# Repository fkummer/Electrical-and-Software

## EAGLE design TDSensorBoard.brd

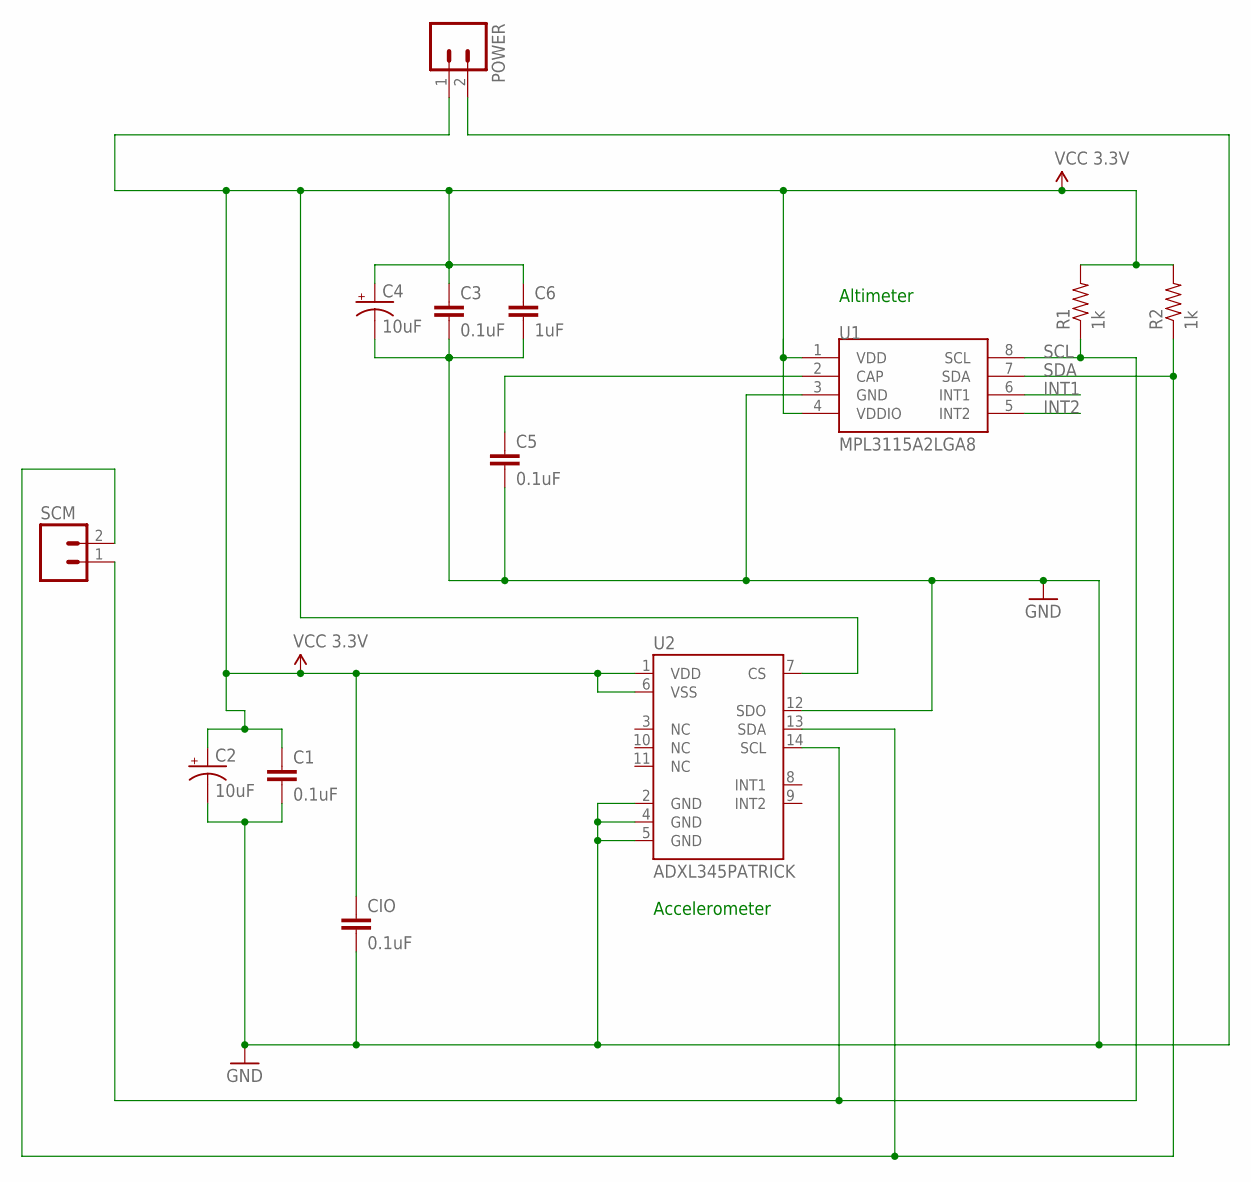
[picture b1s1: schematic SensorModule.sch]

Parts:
C1, C3, C5: 0.1uF; CAP-PTH-SMALL
C2, C4: 10uF; CPOL-RADIAL-10UF-25V
C6: 1uF; CAP-PTH-SMALL
CIO: 0.1uF; CAP-PTH-SMALL
POWER: M02PTH; 1X02
R1, R2: 1k; AXIAL-0.4
SCM: M02PTH; 1X02
U1: MPL3115A2LGA8; LGA8
U2: ADXL345PATRICK; LGA14_1:1_PATRICK

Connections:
GND: C1.2, C2.2 (-), C3.2, C4.2 (-), C5.2, C6.2, CIO.2, POWER.2, U1.3 (GND), U2.2 (GND), U2.4 (GND), U2.5 (GND), U2.12 (SDO)
INT1: U1.6 (INT1)
INT2: U1.5 (INT2)
unnamed: C5.1, U1.2 (CAP)
SCL: R1.P$1 (1), SCM.1, U1.8 (SCL), U2.14 (SCL)
SDA: R2.P$1 (1), SCM.2, U1.7 (SDA), U2.13 (SDA)
VCC_3.3V: C1.1, C2.1 (+), C3.1, C4.1 (+), C6.1, CIO.1, POWER.1, R1.P$2 (2), R2.P$2 (2), U1.1 (VDD), U1.4 (VDDIO), U2.1 (VDD), U2.6 (VSS), U2.7 (CS)

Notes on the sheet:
Altimeter
Accelerometer

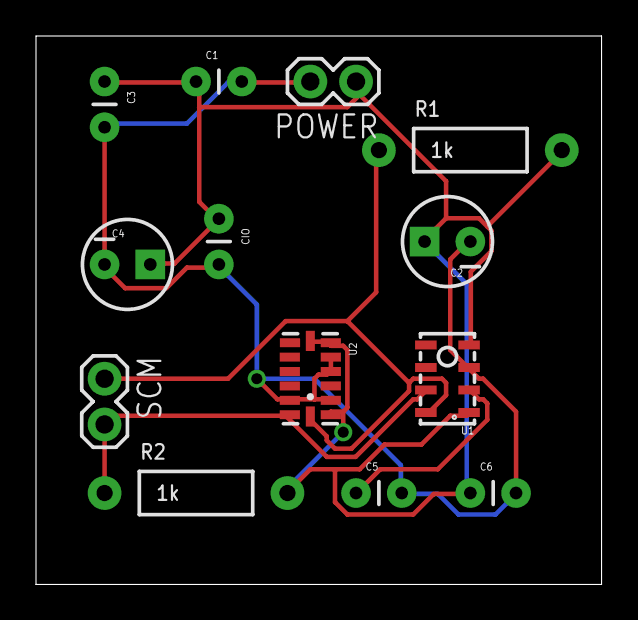
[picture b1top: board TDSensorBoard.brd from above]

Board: 2 copper layers, 31.4 x 30.5 mm, 13 parts (0 on the bottom side), 5 nets.

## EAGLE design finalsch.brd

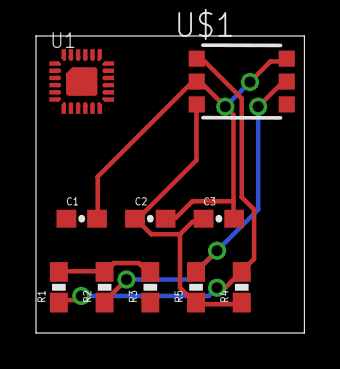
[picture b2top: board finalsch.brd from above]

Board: 2 copper layers, 14.9 x 16.5 mm, 10 parts (0 on the bottom side), 7 nets.

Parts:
C1, C2: 0.1uF; 0603-CAP
C3: 100 nF; 0603-CAP
R1, R2, R3, R4, R5: 10K; 0603-RES
U1: MPU-9250; QFN24_PAD
U$1: MS580602BA52-51'A'; MS5806-02BA

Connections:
CS: R3.1, U1.22
GND: C1.2, C2.2, C3.2, U1.9, U1.11, U1.18, U1.20, U1.CENTER, U$1.P$2, U$1.P$4
REGOUT: C1.1, U1.10
SCL/SCLK: R2.1, R5.2, U1.23, U$1.P$5
SDA/SDI: R1.1, R4.2, U1.24, U$1.P$1
VDD: C2.1, C3.1, R4.1, R5.1, U1.13, U$1.P$3
VDDIO: R1.2, R2.2, R3.2, U1.1, U1.8

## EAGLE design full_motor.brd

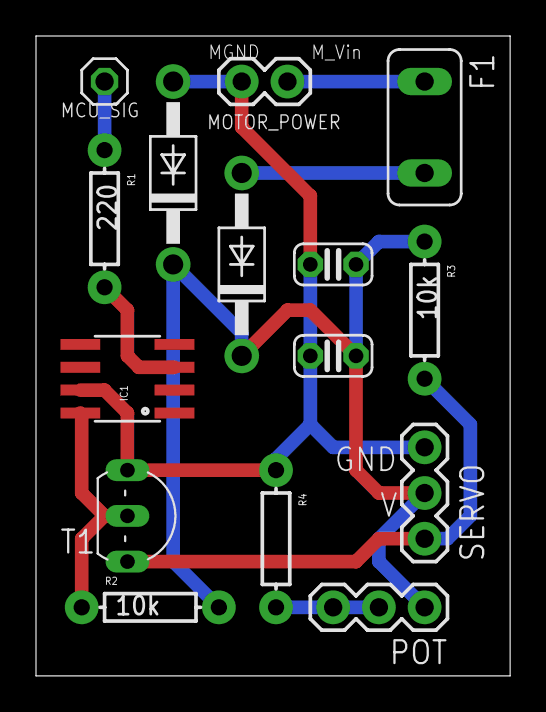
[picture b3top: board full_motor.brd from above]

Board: 2 copper layers, 26.3 x 35.5 mm, 15 parts (0 on the bottom side), 9 nets.

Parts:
C1, C2: 0.1uF; C025-024X044
D3, D4: 1N4004; DO41-10
F1: 3A; TE5
IC1: ILD213T; SO08
MCU_SIG: 1X01
MOTOR_POWER: 1X02
POT: 1X03
R1: 220; AXIAL-0.3EZ
R2, R3: 10k; AXIAL-0.3EZ
R4: AXIAL-0.3EZ
SERVO: SMALL_SERVO; 1X03
T1: 2N2222; TO92-EBC-OVAL

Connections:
6V_POWER: C1.1, C2.1, D3.C, D4.C, POT.1, R2.P$2, R3.P$1, SERVO.2
GND_MOTOR: C1.2, C2.2, D4.A, IC1.7, MOTOR_POWER.2, R4.P$1, SERVO.3, T1.E
MCU_FEEDBACK: POT.2, POT.3, R4.P$2
unnamed: IC1.3, R1.P$2
unnamed: IC1.8, R2.P$1, T1.B
unnamed: D3.A, F1.2
unnamed: R3.P$2, SERVO.1, T1.C
TO_MCU: MCU_SIG.1, R1.P$1
TO_POWER_6V: F1.1, MOTOR_POWER.1

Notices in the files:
parts and their libraries:
SparkFun-Sensors: Licensing: CC v3.0 Share-Alike You are welcome to use this library for commercial purposes.
SparkFun-Passives: Licensing: Creative Commons ShareAlike 4.0 International - https://creativecommons.org/licenses/by-sa/4.0
